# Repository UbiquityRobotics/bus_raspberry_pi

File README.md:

# bus_raspberry_pi

Raspberry Pi that can be connected to a bus.

The bus is a half-duplex multi-drop bus that runs at 500 Kbps.
It uses a Microchip MCP2562 CAN bus transceivers to connect to
the bus.

## Firmware

The software environment for the bus_raspberry_pi is more complicated
than we would like.  The bus_raspberry_pi deliberately uses
an ATmega324P microcontroller to be as compatible as possible
with the Arduino community.  Unfortunately, about the only
board out there that used the '324P is the Sanguino and it
rapidly fell out of use.  Thus, '324P support is a bit more
complicated than we would like.  The key thing is that we have
forked a version of the Arudino repository to add '324P support.
Please note, that our fork of the Arduino system only adds '324P
support and nothing else.  Thus, we should have no problems tracking
the main portions of the Arduino code base.

In addition, the Arduino-IDE does not play nice with version
control systems.  So, we use a fairly popular alternative called
`Arduino-Makefile` which uses fairly standard Makefiles and
standalone editors (e.g. `vim` or `emacs`) to develop Arduino
code that is complatible with the Arduino IDE.

### Installing the Bootloader

(To be written up)

### Installing the Arduino-Makefile Development Environment

To set things up:

        cd .../catkin_ws/src
        git clone https://github.com/UbiquityRobotics/Arduino-Makefile.git
        git clone https://github.com/UbiquityRobotics/bus_common.git
        git clone https://github.com/UbiquityRobotics/bus_raspberry_pi.git
        git clone https://github.com/UbiquityRobotics/bus_server.git
        git clone https://github.com/UbiquityRobotics/bus_slave.git
        # The following command downloads ~2GB of version control stuff.
	# Even with a fast link it takes a while...
        git clone https://github.com/UbiquityRobotics/Arduino.git

Next, we need to bring over all the compilers and stuff to support
the AVR compilation environment:

        sudo apt-get avr-libc avrdude binutils-avr gcc-avr
	# We also need GNU make:
        sudo apt-get install build-essential

When all of the dust settles, you should be able to do the following:

        cd .../catkin_ws/src/bus_raspberry_pi
        make
        make upload       # Read below for more about uploading

The upload target expects you to have USB-serial cable
plugged into your laptop/desktop.  We use the DFRobot
FTDI Basic Breakout board.  This board has two features
that we like:

* One you can select between 3.3V and 5V.  We always use 3.3V.
  Ground is pin 1 and plugs into pin 1 of N4 on the
  bus_raspberry_pi.

* It puts DTR on pin 6 instead of RTS.  The DTR signal is
  what the Arduinos use for their reset signal.

This board requires a USB-A to mini-USB-B cable.  We purchased
ours from Jameco (part number: 2152243.)

### The Firmware

The actual code that implements the firmware starts in
`bus_raspberry_pi.ino`.  The key line is:

        #define TEST TEST_...

The values for `TEST_...` are found in `../bus_server/bus_server.h`:

* `TEST_BUS_OUTPUT` outputs a stream of chacters on the serial port.
* `TEST_BUS_ECHO` is a strange bus debugging mode (too hard to explain.)
* `TEST_BUS_COMMAND` blinks an LED on the motor controller board.
* `TEST_BUS_BRIDGE` runs the software as a bus bridge.
* `TEST_BUS_LINE` runs the ROS Arduino Bridge protocol.

## Revision A

The schematic can be found in the `rev_a` folder as
`bus_raspberry_pi.pdf`.

### Power Supply

The power comes in on either N1 or N2.  These two connectors
are "daisy-chained" so that power can be routed to other boards.
The power goes through Q1 -- a P-channel MOSFET with a very low
R<Sub>ds</Sub>.  Q1 is used to prevent reverse polarity damage
just in case the power comes in reversed.  The power continues
to N6 which is a 5V DC-to-DC power converter that provides up
to 1.5 Amperes of output.  The 5V converter takes a nominal 24V
input with an absolute maximum of 36V.

### Bus Connection

The bus connection is on N3, which is a 2x5 .1 inch pitch
shrouded header.  LGND1 and LGND2 are connected to ground.
CANH and CANL are routed over to U2 which is the CAN bus
(more correctly -- a ISO-11898) transceiver -- a Microchip
MCP2562.  The TXD and RXD outputs are routed to the RXD1 and
TXD1 pins on the ATmega324P processor (U3).

### ISP Connection

The ISP connector is the 2x3 .1 inch pitch connector (N7)
that is connected to the MOSI, MISO, #RESET, and SCK pins
on the processor (U3).

### JTAG Connection

The JTAG connector is N9 which is also a .1 inch 2x5 shrouded
header.  The TDI, TDO, DMS, TCK, and #RESET lines are connected
to the appropriate JTAG pins on the processor (U3).

### 3.3 vs 5V Volt Issues

The processor (U3), AND gates (U1), and CAN bus transceiver (U2)
all run at 5V.  The USB to serial connectors (N4, N5) and the
Raspberry Pi connector (N10) use 3.3V signal levels.  Thus,
there are numerous places where 3.3V vs. 5V signal levels have
to be dealt with.

The signal level conversion is done with a 74HCT08 quad 2-input
AND gate (U1).  The HCT logic family is capable of converting TTL
voltage levels into "high" and "low" signals.  In particular,
the HCT logic family treats any voltage above 2.0V as a logic
"high."

There are 7 separate 22K/33K voltage dividers used for voltage
level issues.  The seven 22K resistors are contained in an 8-pin
SIP (Serial In-line Package.)  These seven resistors are named
R1A through R1F.  Likewise, the seven 33K resistors are contained
in another 8-pin SIP and are named R2A through R2F.  The voltage
dividers are deliberately arranged so that they have the letter
suffix -- R1A/R2A, ... , R1F/R2F.

The nominal center tap voltage of a 22K/33K voltage divider is:

    Vin * 33K/(22K+33K) = Vin * 3/5.

With Vin equal to 5 volts, the center tap voltage is 5V * 3/5 = 3V.

These 8-pin serial in-line packages have a resistance tolerance
of 2%.  This results in a center tap voltage range from 2.88V
to 3.12V.  2.88V is greater than the 2.0 Vih<Sub>min</Sub> for
the HCT logic family.  2.88V is also greater than .7*Vcc
(=.7*3.3V=2.31V) which is the standard Vin<Sub>min</Sub> for
standard CMOS.  3.12V is less than VCC (=3.3V).  Hence, the
voltage divider does not produce illegal 3.3V signaling levels.

Whenever a 5V output needs to be converted from 5 volts to 3V,
it directly fed into a voltage divider.  This occurs with R1D/R2D
connected to TXD0 of the processor (U4) and R1E/R2E and the
output of U1C.

The remaining five voltage dividers are all inputs of the 
74HCT08 quad AND gate package.  There are three cases to
be considered:

* When there is no connection, the voltage divider will 
  pull the input pin to a nominal 3V which is treated as
  a logic high.

* a 3.3V signal is connected, it will be at either 0V or 3.3V.
  In either case, the provided 3.3V voltage signal "overrides"
  the voltage divider.

* For the USB to serial connectors (N4, N5), it is possible
  to accidentally connect in a 5V USB to serial cable.  Again,
  in this case, the provided 5V voltage signal "overrides"
  the voltage divider.  The 74HCT05 is perfectly happy to
  tolerate a 5V input signal.

### Reset Circuitry

The reset signal can be sourced from four locations:

* The manual reset push button -- SW1,

* The #NRST on the JTAG connector (N9),

* The GPIO18 pin on N10, and

* The #RTS signal (3.3V) on the programming FTDI connector (N4),

The push button is the simplest.  It connects the #RESET line
to ground when pushed.  Done.

Similarly, the #NRST line on the JTAG connector (N9) can be
driven low by a JTAG programmer/debugger.  Done.

Both the #RTS signal from N4 and the GPIO18 pin from N10
are used to trigger temporary reset pulse.  The basic
circuit is C6, D1 and R4 for #RTS/N4 and C8, D1 and R4.
Since the circuit is basically the same for both branches,
only the #RTS/N4 branch is explained.

The reset circuit from #RTS/N4 adheres to the Arduino defacto
standard for reset.  The signal comes in on pin 2 of U1A.
A voltage divider R1B/R2B holds the line at a nominal 3V
if no serial cable is plugged in.  Pin 1 of U1A is tied
to 5V so that U1A operates as a simple 3.3V to 5V voltage
level converter.

When the Arduino programmer (usually AVRDUDE) opens the connection
to the serial cable, #RTS (Request to Send) is driven low
for the duration of the programming session.  Capacitor C6, D1,
and R4 are used to convert the falling edge of #RTS into a
pulse onto the #RESET line.

* Prior to asserting #RTS low, the U1A 5V output and the
  R4 10K pull-up resistor hold both ends of capacitor C6
  at 5V.  This completely discharges C6.

* When #RTS goes low at the start of programming, the U1A
  output also goes low.  Since there is no voltage across
  C6, the other end of C6 is driven low as well.  This
  causes the #RESET line to be asserted low.

* Now C6 starts getting charged via R4 and starts to develop
  5V across C6.  Eventually the voltage across C6 will get
  high enough to de-assert #RESET and the processor (U3)
  will start to run the boot-loader.o

* When the programming session is over, #RTS is driven high.
  The causes the output of C6 to attempt to jump from 5V
  up to 10V.

<Pre>
        10V |                           *
            |                           **
            |                           * ***
            |                           *    ****
            |                           *        *****
        5V  ********              *******             *******
            |      *        ******      ^
            |      *    ****            |
            |      * ***                |
            |      **                   |
        0V  +------*--------------------|----------------------->
                                        |
                   ^                    |
                   |                    |
               #RTS goes low       #RTS goes high
</Pre>

* To prevent the voltage from going up to 10V, the Schottky
  diode D1 clamps the voltage to no more than 5.2V by very
  rapidly discharging C6.

The reason why a Schottky diode is used instead of a silicon
diode is because it unclear what the voltage tolerance of #NRST
of the JTAG programmer connector (N9) and the #RESET connector
of the ISP connector (N7) are.  By using a Schottky diode,
the voltage is clamped to 5.2V rather than 5.7.

### RXD and TXD Considerations

In general, the primary purpose of this board is to connect
TXD0 and RXD1 to GPIO15_RXD and GPIO14_TXD respectively.
In addition, it is desirable to allow the programming
connector (N5) to be used to program the processor (U4)
*and* to use the console connector (N5) to view the console
traffic from the Raspberry Pi on boot up.  To accomplish this
task some additional circuitry is used to OR the serial
cable TXD signals into the correct locations.

A key thing to understand about serial connections is that
the line idles "high".  U1B and U1D are AND gates.  Using
De Morgan's law, A.B = ~(~A + ~B).  Thus, using 2-input AND
gates, the signals a correctly OR'ed together so that when
both inputs are idling "high", the output is also "high".

There are three paths to follow:

* Processor (U4) <==> Raspberry Pi (N9),

* Processor (U4) <==> programmer connector (N2), and

* Processor (U4) <==> console connector (N3).

#### Processor to Raspberry Pi

In this situation, the 5V TXD0 output on the processor (U3)
is routed through the R1D/2D voltage divider to bring the
voltage down to a nominal 3.0V.  This signal is routed to U1C.
U1C converts the 3.0V signal to a 5V output which is again
divided back down to 3.0V via R1E/R2E.  This 3.0V signal goes
into GPIO15_RXD on the Raspberry Pi.

In the reverse direction, the 3.3V output of GPIO15_TXD is
sent through the R1G/R2G voltage divider U1B which converts
it to a 5V output and directs it to RXD0 on the processor (U3).

#### Processor to Programmer Connector

In this situation, the 5V TXD0 output on the processor (U3)
is voltage divided by R1D/R2D down to 3.0V and goes to RXD
on the programmer connector (N2).

The 3.3V TXD output on the programmer connector (N2) is
routed to U1B which converts it up to 5V and routes the
signal into RXD0 input on the processor (U4).

#### Processor to Console Connector

In this situation, the 5V TXD0 output on processor (U4)
is voltage divided R1D/R2D down to 3.0V and to both U1C
and the RXD signal of N4.

The GPIO14_TXD is routed through the R1G/R2G voltage
divider directly to the RXD pin of N5.

### LED Circuit

The LED circuit is provides a single LED (D2) that can be

* connected to the power supply to provide a power on LED, or

* connected to PB7/SCK (aka the Arduino D13 pin) of the
   processor (U3), or

* can be left unconnected.

This is accomplished using J1, R5, R6 and D2.

When pins 1 and 3 of J2 are shorted using a jumper, power is
routed from +5V through R6 through the LED (D2) to ground.

When pins 2 and 3 of J2 are shorted together, the output
of PB7/SCK of the processor (U3) is routed through R5 
through the LED to ground.

When pins 3 and 4 of J2 are shorted together, there is
no circuit path through LED (D2).

When pins 1 and 2 of J2 are accidentally shorted together,
resistors R5 and R6 form a voltage divider that simply
wastes power.  At least it does not accidentally short
the power supply to ground.

### Revision B and C Issues

The following issues need to be worked on:

* The two mounting holes on the right are too close to the
  SIP9 resistor.

* Realistically, the processor should be run at 5V in order
  run the crystal at 16MHz.

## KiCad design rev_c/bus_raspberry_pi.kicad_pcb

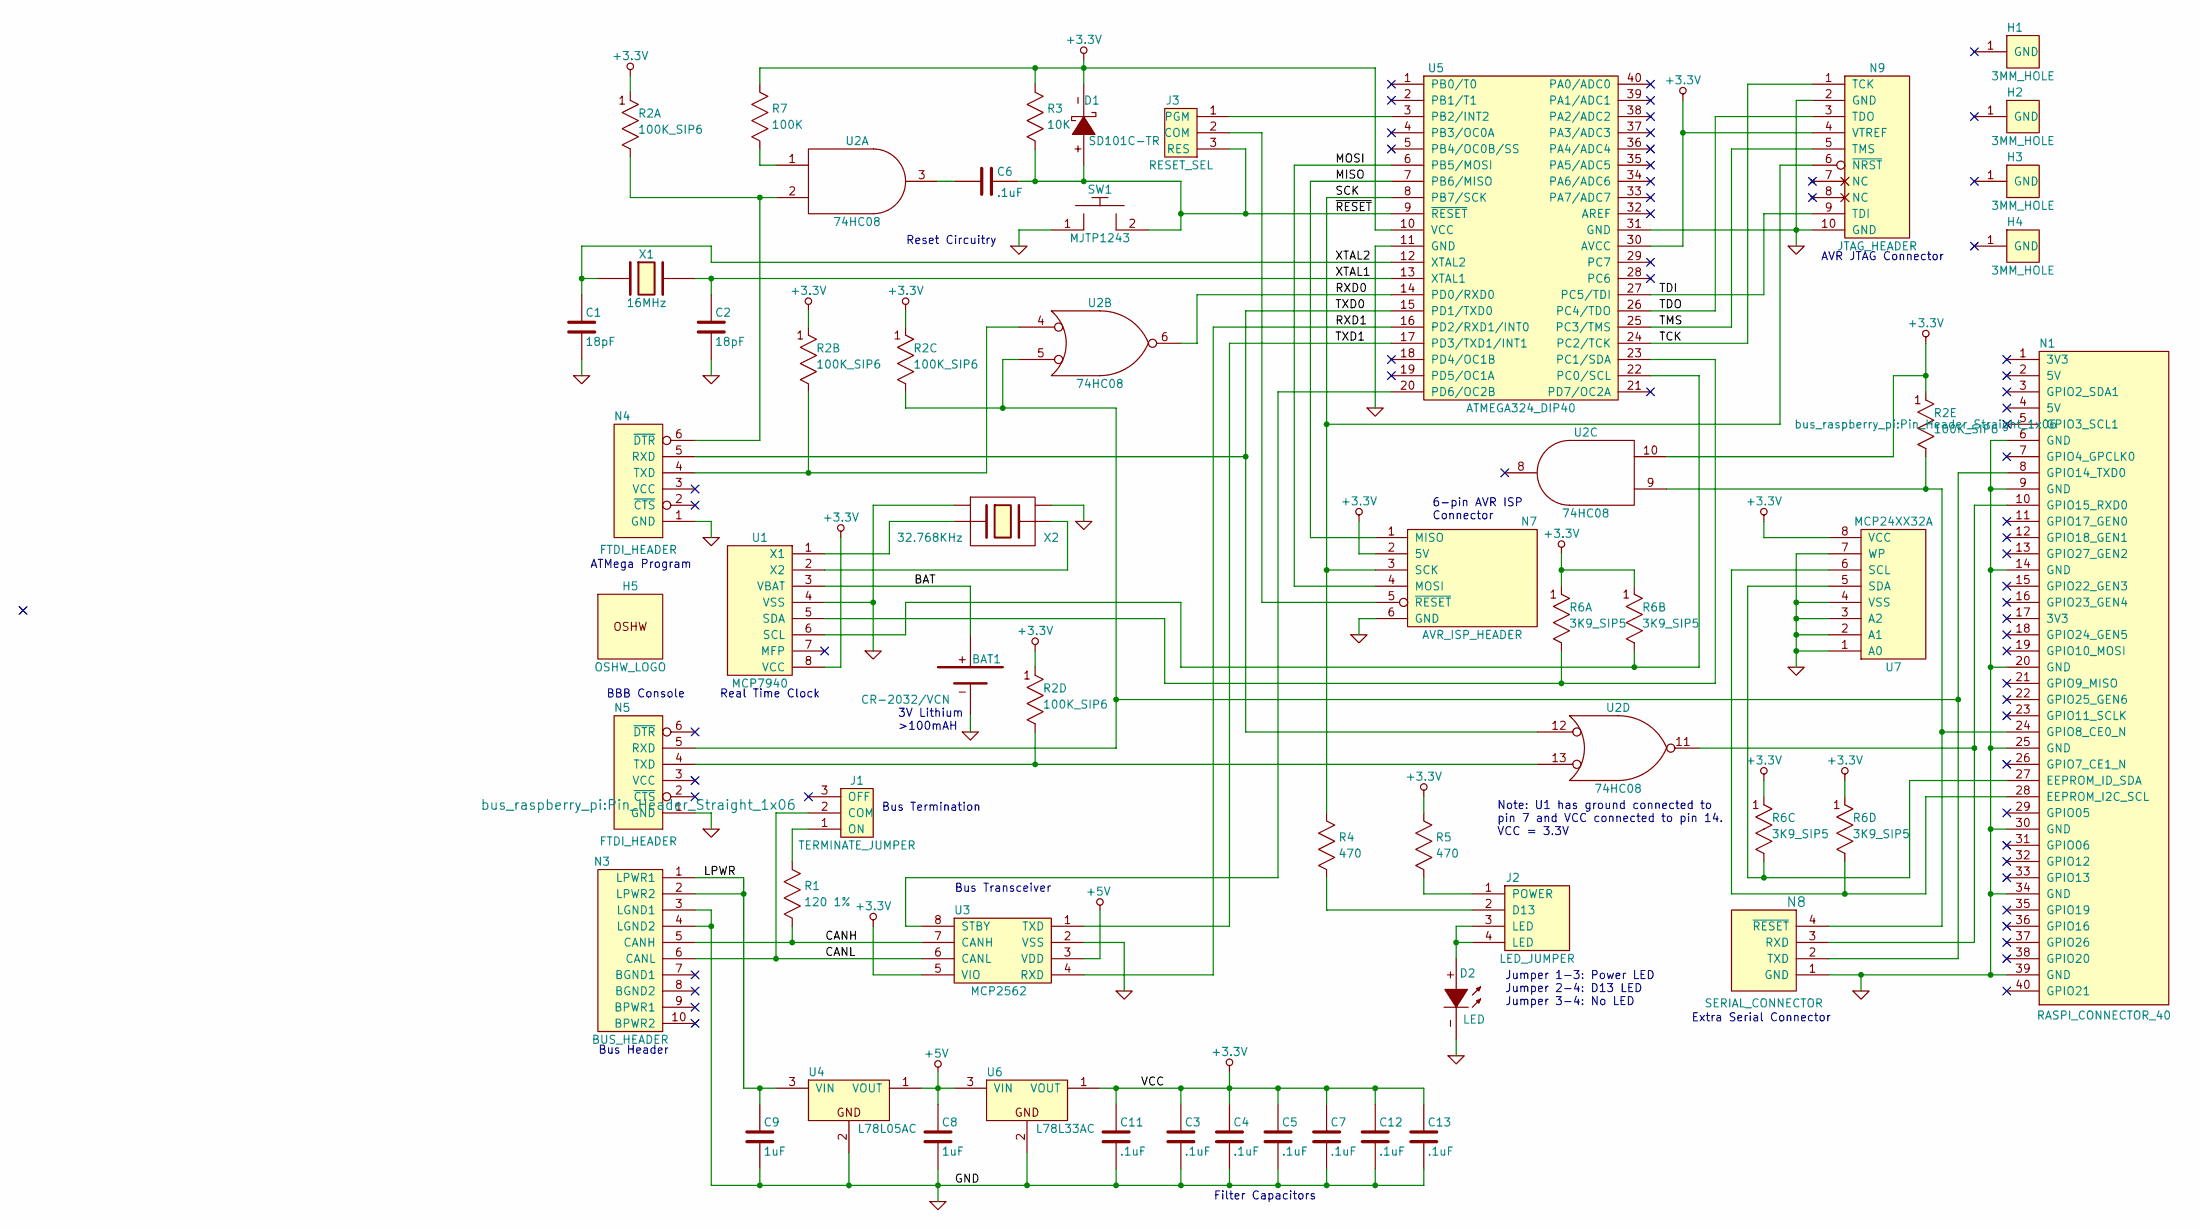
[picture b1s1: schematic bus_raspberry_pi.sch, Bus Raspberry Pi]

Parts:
BAT1: CR-2032/VCN; 10MM_BATTERY
C1, C2: 18pF; Capacitor3MMDiscRM2.5
C3, C4, C5, C6, C7, C11, C12, C13: .1uF; Capacitor3MMDiscRM2.5
C8, C9: 1uF; Capacitor3MMDiscRM2.5
D1: SD101C-TR; Diode_DO-41_SOD81_Horizontal_RM10
D2: LED; T1_LED
H1, H2, H3, H4: 3MM_HOLE; MountingHole_3mm
H5: OSHW_LOGO; OSHW_LOGO_250mil
J1: TERMINATE_JUMPER; Pin_Header_Straight_1x03
J2: LED_JUMPER; Pin_Header_Straight_2x02
J3: RESET_SEL; Pin_Header_Straight_1x03
N1: RASPI_CONNECTOR_40; Pin_Header_Straight_2x20
N3: BUS_HEADER; Pin_Header_Straight_2x05_Shrouded
N4, N5: FTDI_HEADER; Pin_Header_Straight_1x06
N7: AVR_ISP_HEADER; Pin_Header_Straight_2x03
N8: SERIAL_CONNECTOR; Pin_Header_Straight_1x04
N9: JTAG_HEADER; Pin_Header_Straight_2x05_Shrouded
R1: 120 1%; Resistor_Horizontal__400
R2: 100K_SIP6; Pin_Header_Straight_1x06
R3: 10K; Resistor_Horizontal__400
R4, R5: 470; Resistor_Horizontal__400
R6: 3K9_SIP5; Pin_Header_Straight_1x05
R7: 100K; Resistor_Horizontal__400
SW1: MJTP1243; Button_6.5MM
U1: MCP7940; DIP-8__300
U2: 74HC08; DIP-14__300
U3: MCP2562; DIP-8__300
U4: L78L05AC; TO92_123
U5: ATMEGA324_DIP40; DIP-40__600
U6: L78L33AC; TO92_123
U7: MCP24XX32A; DIP-8__300
X1: 16MHz; Crystal_HC49-U_Vertical
X2: 32.768KHz; RTC_CRYSTAL

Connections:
+5V: C8.1, U3.3 (VDD), U4.1 (VOUT), U6.3 (VIN)
/BAT: BAT1.+, U1.3 (VBAT)
/CANH: N3.5 (CANH), R1.1, U3.7 (CANH)
/CANL: J1.2 (COM), N3.6 (CANL), U3.6 (CANL)
/LPWR: C9.1, N3.1 (LPWR1), N3.2 (LPWR2), U4.3 (VIN)
/MISO: N7.1 (MISO), U5.7 (PB6/MISO)
/MOSI: N7.4 (MOSI), U5.6 (PB5/MOSI)
/RXD0: U2.6, U5.14 (PD0/RXD0)
/RXD1: U3.4 (RXD), U5.16 (PD2/RXD1/INT0)
/SCK: N7.3 (SCK), N9.6 (~NRST), R4.2, U5.8 (PB7/SCK)
/TCK: N9.1 (TCK), U5.24 (PC2/TCK)
/TDI: N9.9 (TDI), U5.27 (PC5/TDI)
/TDO: N9.3 (TDO), U5.26 (PC4/TDO)
/TMS: N9.5 (TMS), U5.25 (PC3/TMS)
/TXD0: N4.5 (RXD), U2.12, U5.15 (PD1/TXD0)
/TXD1: U3.1 (TXD), U5.17 (PD3/TXD1/INT1)
/XTAL1: C2.1, U5.13 (XTAL1), X1.2
/XTAL2: C1.1, U5.12 (XTAL2), X1.1
/~RESET: C6.2, D1.+, J3.3 (RES), R3.1, SW1.2, U5.9 (~RESET)
GND: BAT1.-, C1.2, C2.2, C3.2, C4.2, C5.2, C7.2, C8.2, C9.2, C11.2, C12.2, C13.2, D2.-, N1.6 (GND), N1.9 (GND), N1.14 (GND), N1.20 (GND), N1.25 (GND), N1.30 (GND), N1.34 (GND), N1.39 (GND), N3.3 (LGND1), N3.4 (LGND2), N4.1 (GND), N5.1 (GND), N7.6 (GND), N8.1 (GND), N9.2 (GND), N9.10 (GND), SW1.1, U1.4 (VSS), U2.7 (GND), U3.2 (VSS), U4.2, U5.11 (GND), U5.31 (GND), U6.2, U7.1 (A0), U7.2 (A1), U7.3 (A2), U7.4 (VSS), U7.7 (WP), X2.3 (GND), X2.4 (GND)
unnamed: C6.1, U2.3
unnamed: D2.+, J2.3 (LED), J2.4 (LED)
unnamed: J1.1 (ON), R1.2
unnamed: J2.1 (POWER), R5.1
unnamed: J2.2 (D13), R4.1
unnamed: J3.1 (PGM), U5.3 (PB2/INT2)
unnamed: J3.2 (COM), N7.5 (~RESET)
unnamed: N1.8 (GPIO14_TXD0), N5.5 (RXD), N8.2 (TXD), R2.4, U2.5
unnamed: N1.10 (GPIO15_RXD0), N8.3 (RXD), U2.11
unnamed: N1.24 (GPIO8_CE0_N), N8.4 (~RESET), R2.6, U2.9
unnamed: N1.27 (EEPROM_ID_SDA), R6.4, U7.5 (SDA)
unnamed: N1.28 (EEPROM_I2C_SCL), R6.5, U7.6 (SCL)
unnamed: N4.4 (TXD), R2.3, U2.4
unnamed: N4.6 (~DTR), R2.2, U2.2
unnamed: N5.4 (TXD), R2.5, U2.13
unnamed: R6.2, U1.5 (SDA), U5.23 (PC1/SDA)
unnamed: R6.3, U1.6 (SCL), U5.22 (PC0/SCL)
unnamed: R7.1, U2.1
unnamed: U1.1 (X1), X2.1
unnamed: U1.2 (X2), X2.2
unnamed: U3.8 (STBY), U5.20 (PD6/OC2B)
VCC: C3.1, C4.1, C5.1, C7.1, C11.1, C12.1, C13.1, D1.-, N7.2 (5V), N9.4 (VTREF), R2.1, R3.2, R5.2, R6.1, R7.2, U1.8 (VCC), U2.10, U2.14 (VCC), U3.5 (VIO), U5.10 (VCC), U5.30 (AVCC), U6.1 (VOUT), U7.8 (VCC)

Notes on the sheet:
BBB Console
ATMega Program
Note: U1 has ground connected to pin 7 and VCC connected to pin 14. VCC = 3.3V
Bus Header
6-pin AVR ISP Connector
Jumper 1-3: Power LED Jumper 2-4: D13 LED Jumper 3-4: No LED
Filter Capacitors
Bus Transceiver
Reset Circuitry
AVR JTAG Connector
3V Lithium >100mAH
Real Time Clock
Bus Termination
Extra Serial Connector

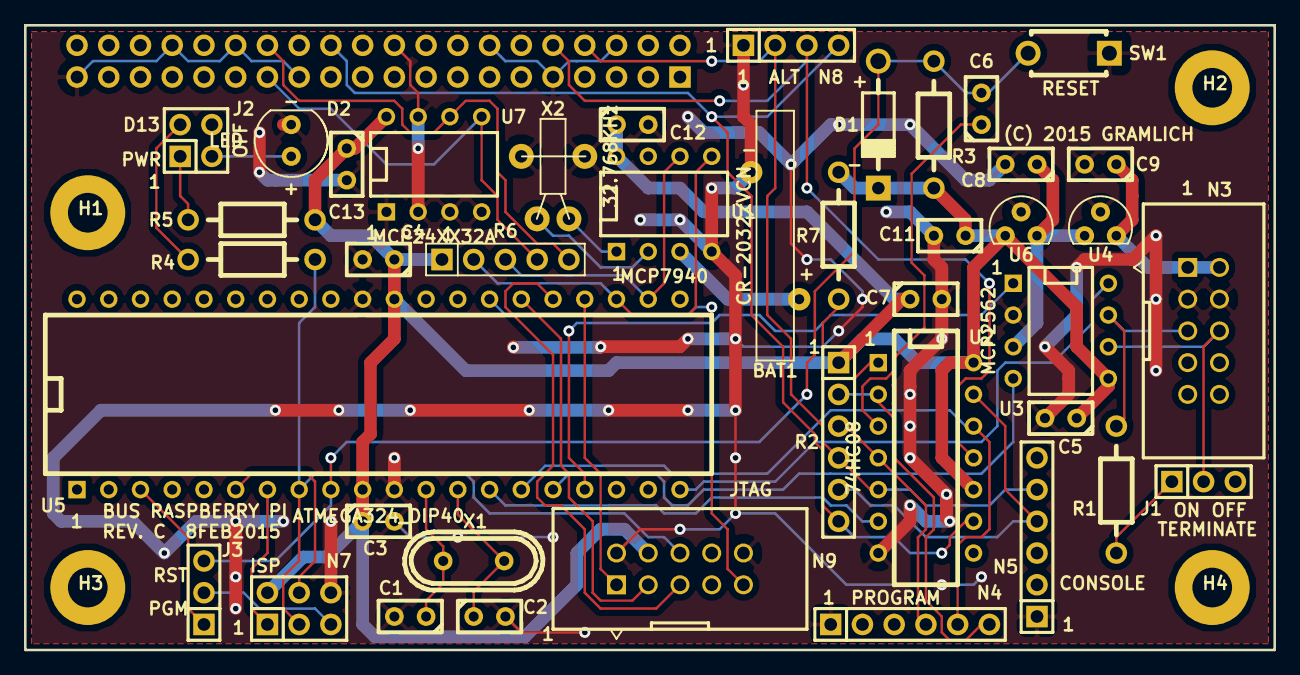
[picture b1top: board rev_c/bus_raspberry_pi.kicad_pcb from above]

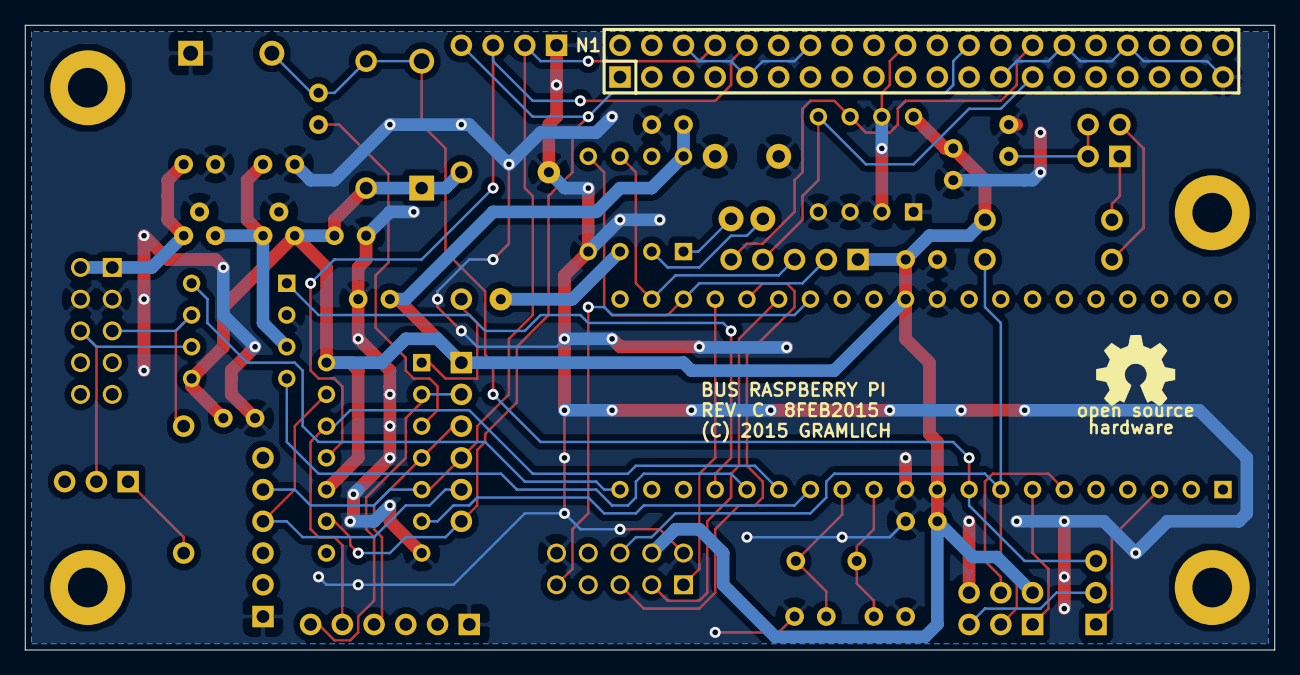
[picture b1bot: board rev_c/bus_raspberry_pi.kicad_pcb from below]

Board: 2 copper layers, 100.0 x 50.0 mm, 47 parts (2 on the bottom side), 42 nets.

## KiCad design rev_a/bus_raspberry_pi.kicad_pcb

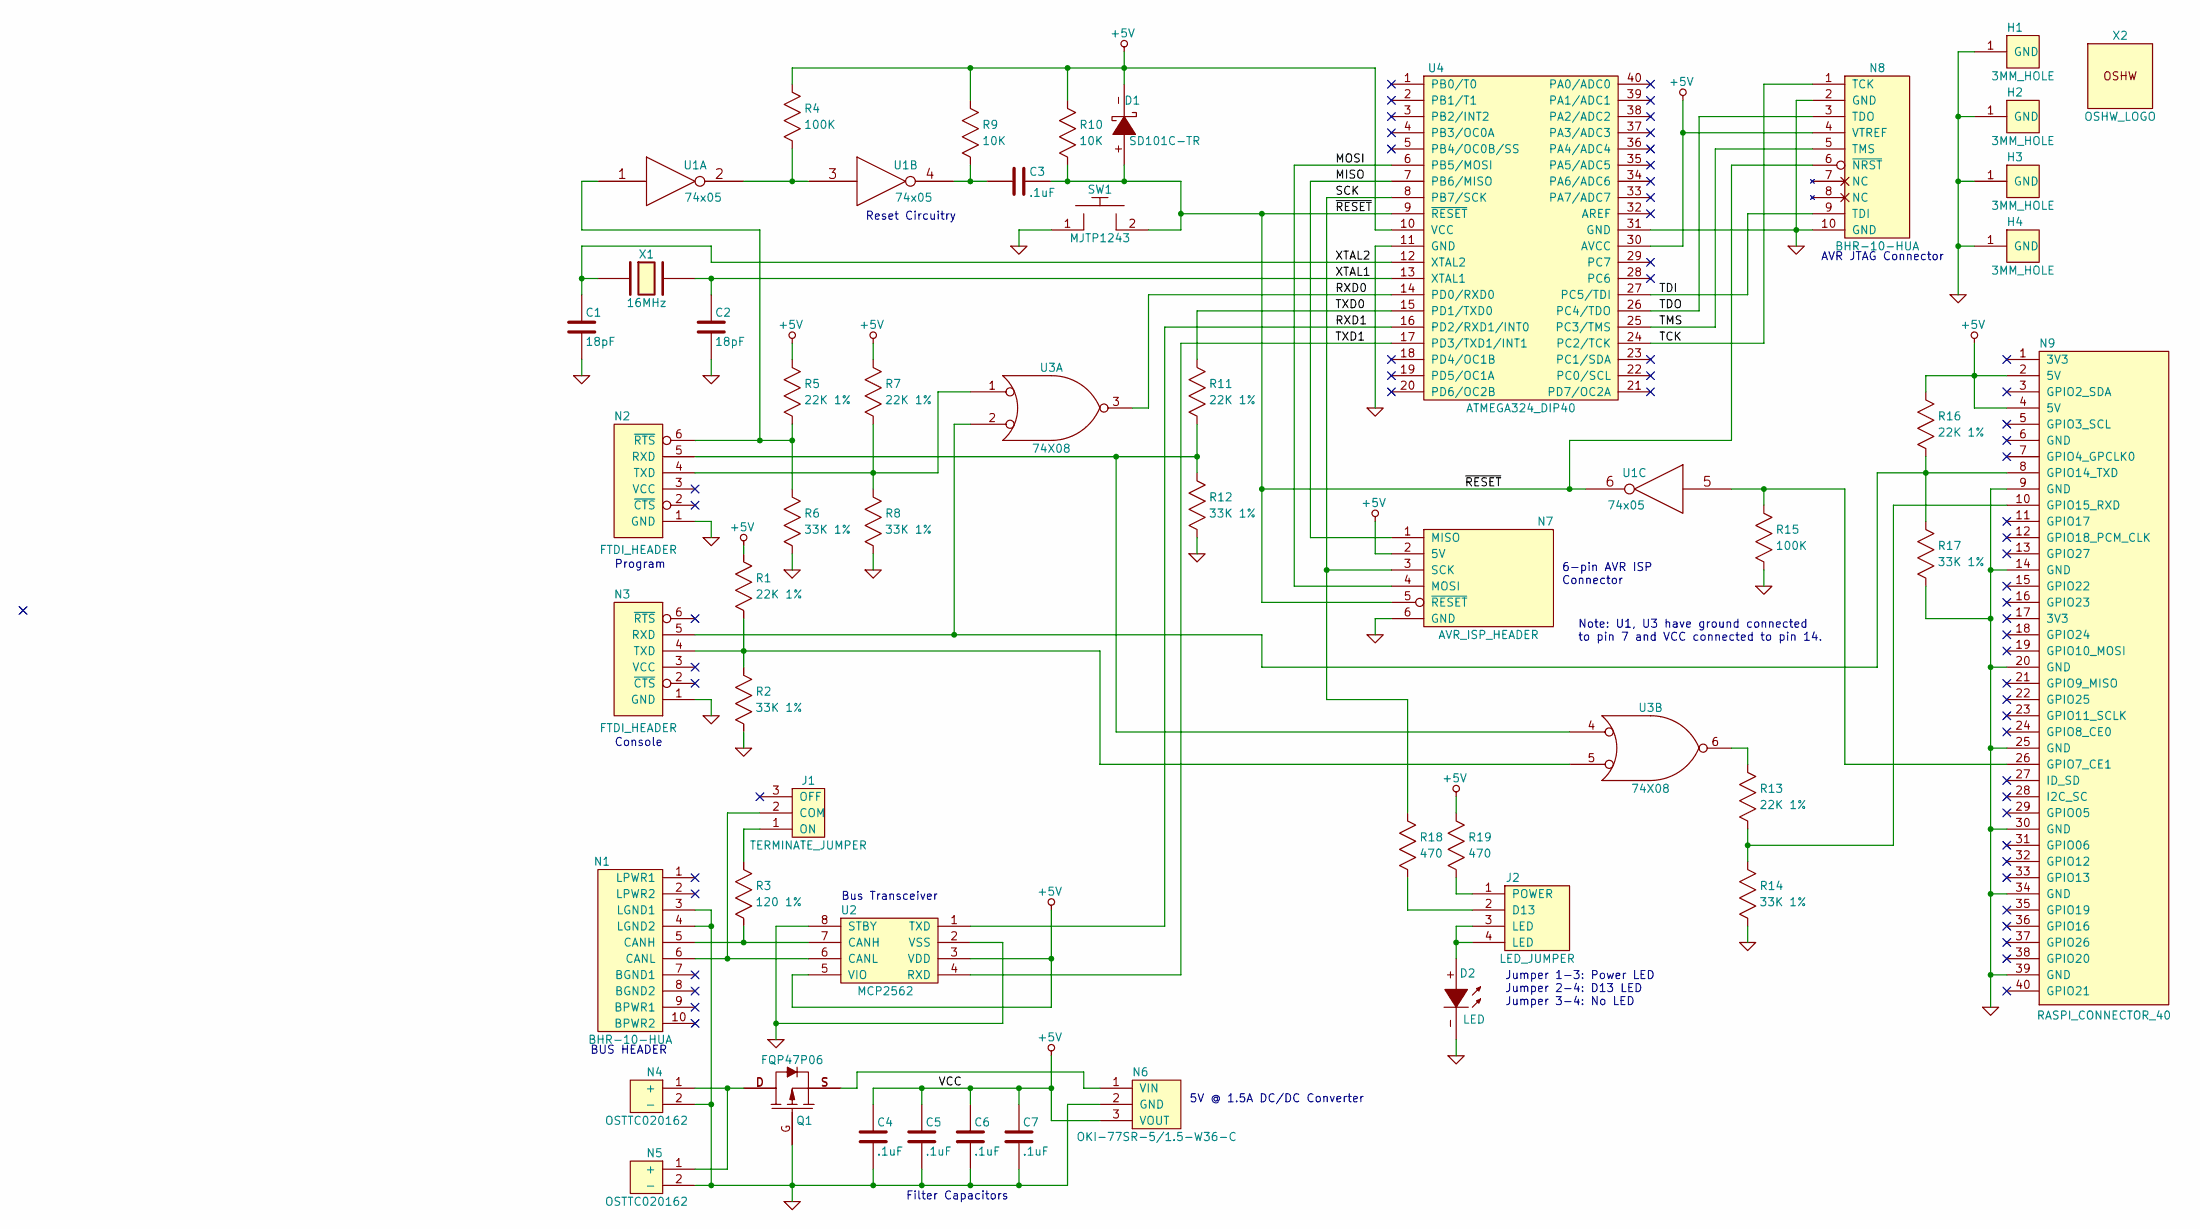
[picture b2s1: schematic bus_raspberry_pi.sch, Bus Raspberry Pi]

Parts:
C1, C2: 18pF
C3, C4, C5, C6, C7: .1uF
D1: SD101C-TR
D2: LED
H1, H2, H3, H4: 3MM_HOLE
J1: TERMINATE_JUMPER
J2: LED_JUMPER
N1, N8: BHR-10-HUA
N2, N3: FTDI_HEADER
N4, N5: OSTTC020162
N6: OKI-77SR-5/1.5-W36-C
N7: AVR_ISP_HEADER
N9: RASPI_CONNECTOR_40
Q1: FQP47P06
R1, R5, R7, R11, R13, R16: 22K 1%
R2, R6, R8, R12, R14, R17: 33K 1%
R3: 120 1%
R4, R15: 100K
R9, R10: 10K
R18, R19: 470
SW1: MJTP1243
U1: 74x05
U2: MCP2562
U3: 74X08
U4: ATMEGA324_DIP40
X1: 16MHz
X2: OSHW_LOGO

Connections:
+5V: C4.1, C5.1, C6.1, C7.1, D1.-, N6.3 (VOUT), N7.2 (5V), N8.4 (VTREF), N9.2 (5V), N9.4 (5V), R1.2, R4.2, R5.2, R7.2, R9.2, R10.2, R16.2, R19.2, U1.14 (VCC), U2.3 (VDD), U2.5 (VIO), U3.14 (VCC), U4.10 (VCC), U4.30 (AVCC)
/MISO: N7.1 (MISO), U4.7 (PB6/MISO)
/MOSI: N7.4 (MOSI), U4.6 (PB5/MOSI)
/RXD0: U3.3, U4.14 (PD0/RXD0)
/RXD1: U2.1 (TXD), U4.16 (PD2/RXD1/INT0)
/SCK: N7.3 (SCK), R18.2, U4.8 (PB7/SCK)
/TCK: N8.1 (TCK), U4.24 (PC2/TCK)
/TDI: N8.9 (TDI), U4.27 (PC5/TDI)
/TDO: N8.3 (TDO), U4.26 (PC4/TDO)
/TMS: N8.5 (TMS), U4.25 (PC3/TMS)
/TXD0: R11.2, U4.15 (PD1/TXD0)
/TXD1: U2.4 (RXD), U4.17 (PD3/TXD1/INT1)
/XTAL1: C2.1, U4.13 (XTAL1), X1.2
/XTAL2: C1.1, U4.12 (XTAL2), X1.1
/~RESET: C3.2, D1.+, N7.5 (~RESET), N8.6 (~NRST), R10.1, SW1.2, U1.6, U4.9 (~RESET)
GND: C1.2, C2.2, C4.2, C5.2, C6.2, C7.2, D2.-, H1.1, H2.1, H3.1, H4.1, N1.3 (LGND1), N1.4 (LGND2), N2.1 (GND), N3.1 (GND), N4.2 (-), N5.2 (-), N6.2 (GND), N7.6 (GND), N8.2 (GND), N8.10 (GND), N9.9 (GND), N9.14 (GND), N9.20 (GND), N9.25 (GND), N9.30 (GND), N9.34 (GND), N9.39 (GND), Q1.G, R2.1, R6.1, R8.1, R12.1, R14.1, R15.1, R17.1, SW1.1, U1.7 (GND), U2.2 (VSS), U2.8 (STBY), U3.7 (GND), U4.11 (GND), U4.31 (GND)
unnamed: C3.1, R9.1, U1.4
unnamed: D2.+, J2.3 (LED), J2.4 (LED)
unnamed: J1.1 (ON), R3.2
unnamed: J1.2 (COM), N1.6 (CANL), U2.6 (CANL)
unnamed: J2.1 (POWER), R19.1
unnamed: J2.2 (D13), R18.1
unnamed: N1.5 (CANH), R3.1, U2.7 (CANH)
unnamed: N2.4 (TXD), R7.1, R8.2, U3.1
unnamed: N2.5 (RXD), R11.1, R12.2, U3.4
unnamed: N2.6 (~RTS), R5.1, R6.2, U1.1
unnamed: N3.4 (TXD), R1.1, R2.2, U3.5
unnamed: N3.5 (RXD), N9.8 (GPIO14_TXD), R16.1, R17.2, U3.2
unnamed: N4.1 (+), N5.1 (+), Q1.D
unnamed: N6.1 (VIN), Q1.S
unnamed: N9.10 (GPIO15_RXD), R13.1, R14.2
unnamed: N9.26 (GPIO7_CE1), R15.2, U1.5
unnamed: R4.1, U1.2, U1.3
unnamed: R13.2, U3.6

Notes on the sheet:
Console
Program
Note: U1, U3 have ground connected to pin 7 and VCC connected to pin 14.
BUS HEADER
6-pin AVR ISP Connector
Jumper 1-3: Power LED Jumper 2-4: D13 LED Jumper 3-4: No LED
5V @ 1.5A DC/DC Converter
Filter Capacitors
Bus Transceiver
Reset Circuitry
AVR JTAG Connector

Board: 2 copper layers, 51 parts (0 on the bottom side), 34 nets, no tracks yet.

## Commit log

2014-08-09 Did schematic for Revision A.
2014-08-10 Next iteration of schematic; started board layout.
2014-08-11 Layed out PCB.
2015-01-12 Made a compy of bus_beaglebone (Rev. D) to start Rev. B of bus_raspberry_pi.
2015-01-13 Revision B is ready for manufacture.
2015-01-15 Converted 74HCT08 => 74HC08 .
2015-01-31 Made a clone of Rev. B.
2015-01-31 Changed from B=>C. Flipped N1.
2015-02-09 Minor changes to Rev. C.
2015-03-05 Added Rev. B and C issues to README.md
2015-03-06 Clone from bus_beaglebone. Some refactoring is needed.
2015-03-06 Refactored shared code into bus_server.
2015-03-06 Moved Frame_Buffer.cpp/h to bus_server.
2015-03-11 Added bus_common to ARDUINO_LIBS path in Makefile.
2015-03-11 Made member of SetPointInfo start with an underscore.
2015-04-24 Did some code refactoring.
2015-05-07 Update README.md.
2015-05-08 Started refactoring Freya/Loki Code.
2015-05-08 Add TEST_RAB_FREYA
2015-05-11 Started transition over to Bridge object.
2015-05-11 More conversion over to Bridge object.
2015-05-11 Pretty much done with Bridge object.
2015-05-11 Added Freya_Motor_Encoder sub-class of Bus_Motor_Encoder.
2015-05-12 Got encoders working.

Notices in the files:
rev_c/bus_raspberry_pi.kicad_pcb:
(C) 2015 GRAMLICH
